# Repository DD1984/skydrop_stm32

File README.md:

this is port of SkyDrop vario to stm32vldiscovery board

origin code:
https://github.com/fhorinek/SkyDrop
website:
http://skybean.eu

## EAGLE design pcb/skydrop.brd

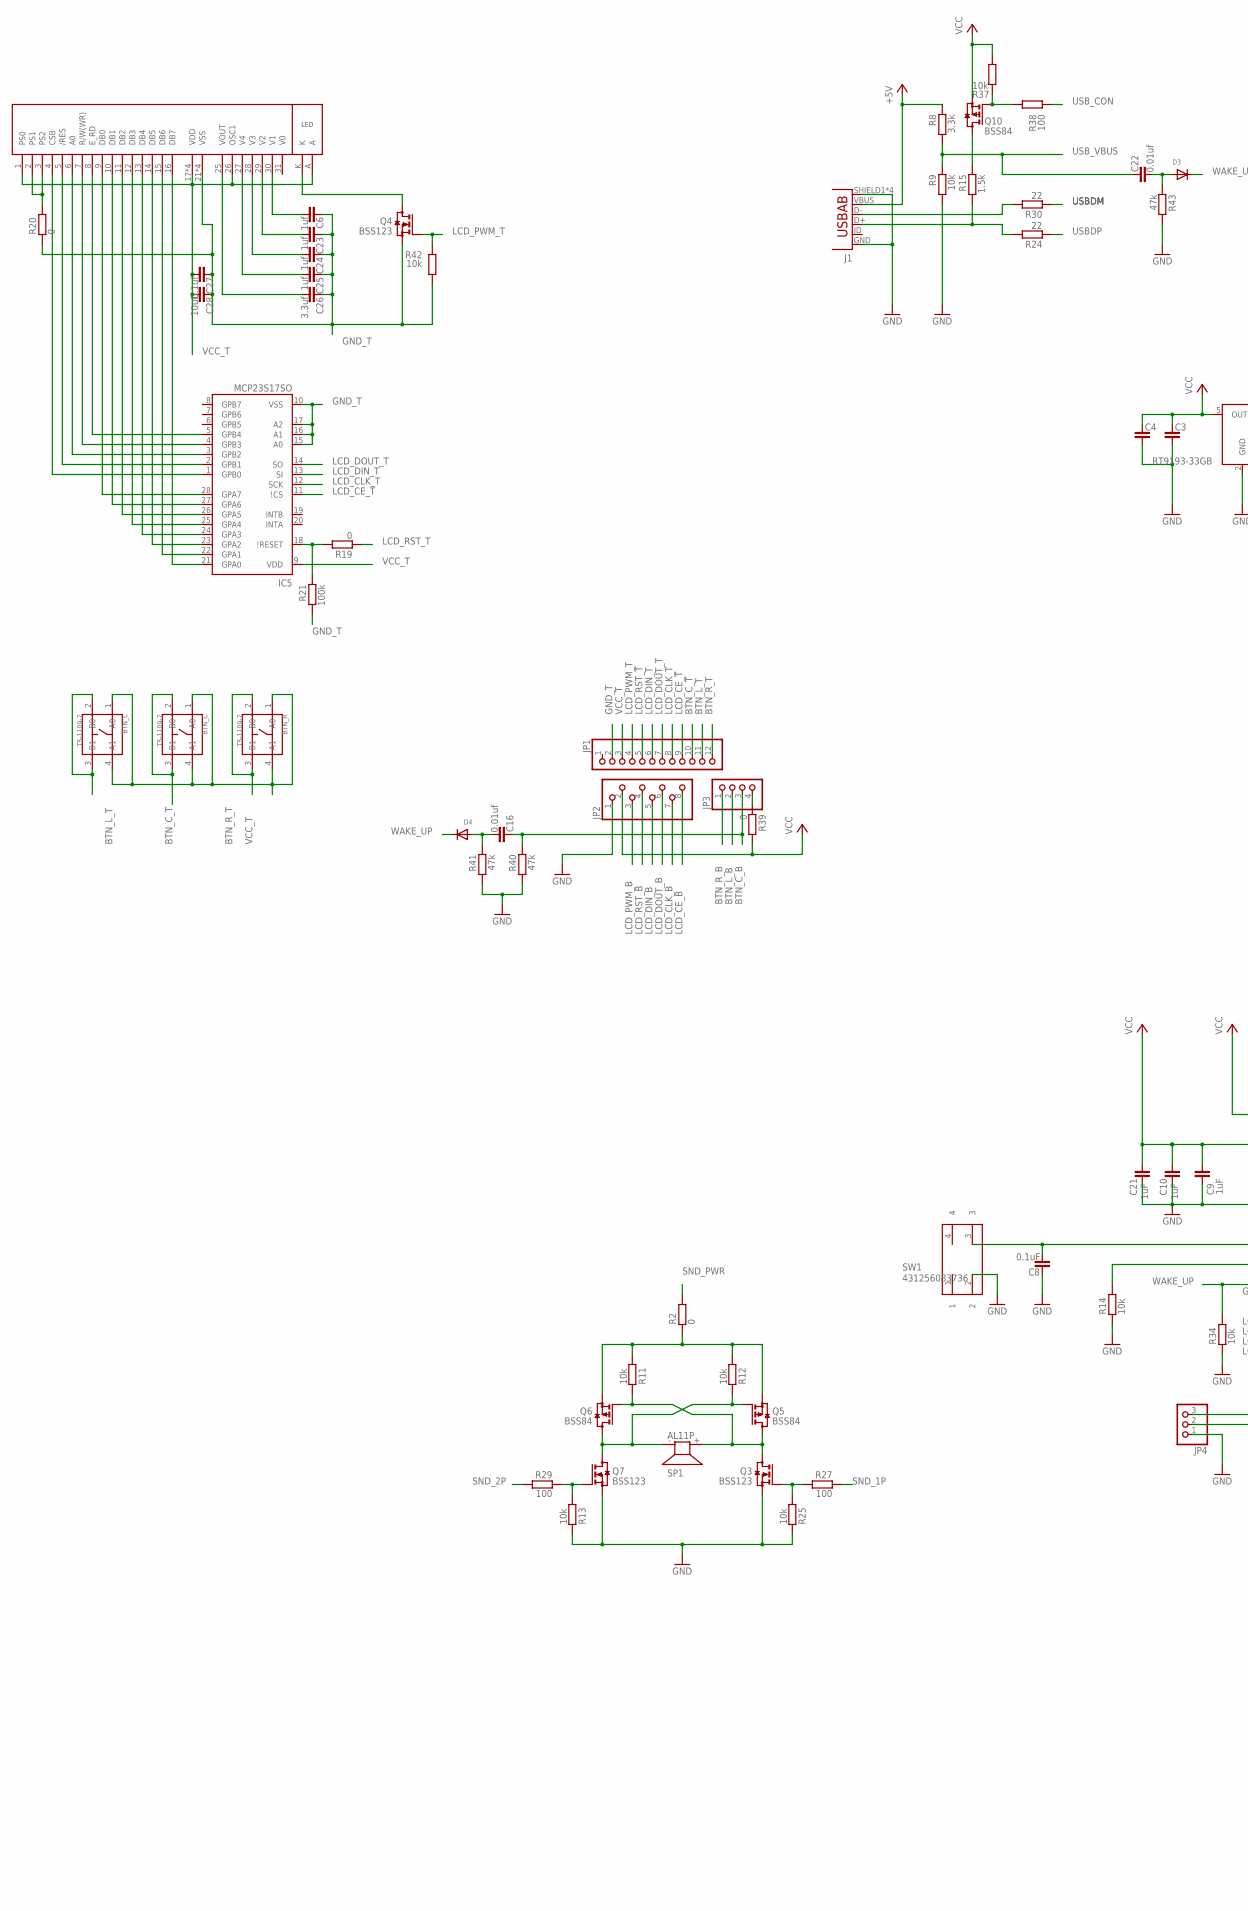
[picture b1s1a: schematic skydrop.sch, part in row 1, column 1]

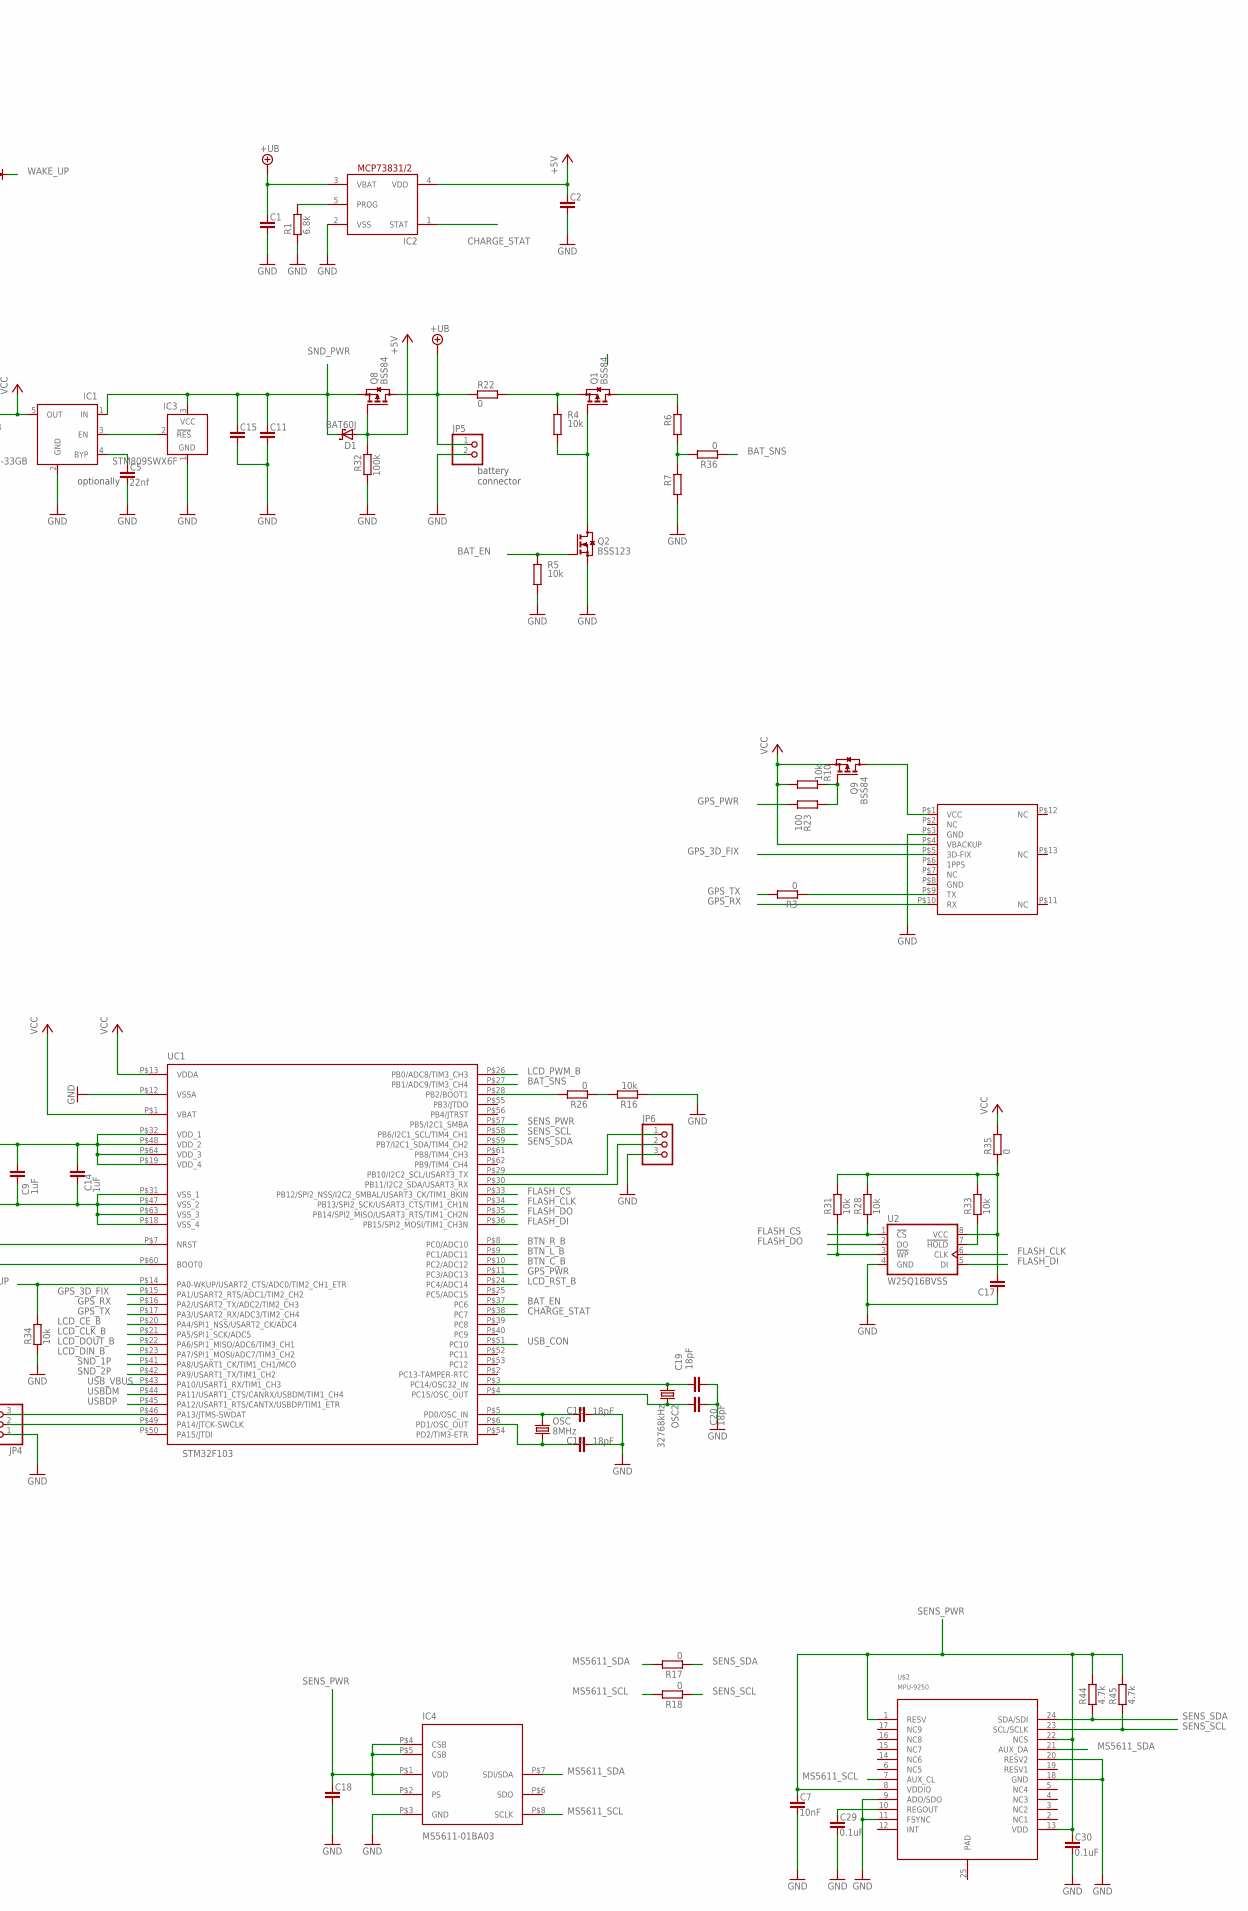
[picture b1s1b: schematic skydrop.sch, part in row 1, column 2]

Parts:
BTN_C: TS-1109-7; SW4-6.2X6.2X5.0MM
BTN_L: TS-1109-7; SW4-6.2X6.2X5.0MM
BTN_R: TS-1109-7; SW4-6.2X6.2X5.0MM
C1, C2, C3, C4, C11, C15, C17, C18: C_0805; C0805
C5: 22nf; C0805
C6, C23, C24, C25: 1uf; C0805
C7: 10nF; C0805
C8, C29, C30: 0.1uF; C0805
C9, C10, C14, C21: 1uF; C0805
C12, C13, C19, C20: 18pF; C0805
C16, C22: 0.01uf; C0805
C26: 3.3uf; C0805
C27: 0.1uf; C0805
C28: 10uf; C0805
D1: BAT60J; SOD323_ST
D3, D4: DIODE_SOD-123FL; SOD-123FL
IC1: RT9193-33GB; SOT23-5
IC2: MCP73831/OT; SOT23-5L
IC3: STM809SWX6F; SOT23B-3
IC4: MS5611-01BA03
IC5: MCP23S17SO; SO28W
J1: USB-AB; USB-AB-MICRO-SMD
JP1: PINHD-1X12; 1X12
JP2: PINHD-1X8; 1X08
JP3: PINHD-1X4; 1X04
JP4, JP6: PINHD-1X3; 1X03
JP5: PINHD-1X2; 1X02
OSC: 8MHz; HC49/S
OSC2: 32768kHz; MM20SS
Q1, Q5, Q6, Q8, Q9, Q10: BSS84; SOT23
Q2, Q3, Q4, Q7: BSS123; SOT23
R1: 6.8k; R0805
R2, R3, R17, R18, R19, R20, R22, R26, R35, R36, R39: 0; R1206
R4, R5, R9, R10, R11, R12, R13, R14, R16, R25, R28, R31, R33, R34, R37, R42: 10k; R0805
R6, R7: R_0805; R0805
R8: 3.3k; R0805
R15: 1.5k; R0805
R21, R32: 100k; R0805
R23, R27, R29, R38: 100; R0805
R24, R30: 22; R0805
R40, R41, R43: 47k; R0805
R44, R45: 4.7k; R0805
SP1: AL11P
SW1: 431256083736
U1: GPS_FGPMMOPA6C; FGPMMOPA6C
U2: W25Q16BVSS; SO08-SS
U$1: NOKIA5110
U$2: MPU-9250; LEAD-QFN24
UC1: STM32F103; TQFP-10X10-64

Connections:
+5V: C2.1, D1.A, IC2.4 (VDD), J1.VBUS, Q8.1 (G), R8.1, R32.1
+UB: C1.1, IC2.3 (VBAT), JP5.1, Q8.3 (D), R22.1
BAT_EN: Q2.1 (G), R5.1, UC1.P$37 (PC6)
BAT_SNS: R36.1, UC1.P$27 (PB1/ADC9/TIM3_CH4)
BTN_C_B: C16.1, JP3.3, R40.1, UC1.P$10 (PC2/ADC12)
BTN_C_T: BTN_C.2 (B0), BTN_C.3 (B1), JP1.10
BTN_L_B: JP3.2, UC1.P$9 (PC1/ADC11)
BTN_L_T: BTN_L.2 (B0), BTN_L.3 (B1), JP1.11
BTN_R_B: JP3.1, UC1.P$8 (PC0/ADC10)
BTN_R_T: BTN_R.2 (B0), BTN_R.3 (B1), JP1.12
CHARGE_STAT: IC2.1 (STAT), UC1.P$38 (PC7)
FLASH_CLK: U2.6 (CLK), UC1.P$34 (PB13/SPI2_SCK/USART3_CTS/TIM1_CH1N)
FLASH_CS: R28.1, U2.1 (!CS!), UC1.P$33 (PB12/SPI2_NSS/I2C2_SMBAL/USART3_CK/TIM1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)
FLASH_DI: U2.5 (DI), UC1.P$36 (PB15/SPI2_MOSI/TIM1_CH3N)
FLASH_DO: U2.2 (DO), UC1.P$35 (PB14/SPI2_MISO/USART3_RTS/TIM1_CH2N)
GND: C1.2, C2.2, C3.2, C4.2, C5.2, C7.2, C8.1, C9.1, C10.1, C11.2, C12.1, C13.1, C14.1, C15.2, C17.1, C18.2, C19.1, C20.1, C21.1, C29.2, C30.2, IC1.2 (GND), IC2.2 (VSS), IC3.1 (GND), IC4.P$3 (GND), J1.GND, J1.SHIELD1 (SHIELD), J1.SHIELD2 (SHIELD), J1.SHIELD3 (SHIELD), J1.SHIELD4 (SHIELD), JP2.1, JP4.1, JP5.2, JP6.3, Q2.2 (S), Q3.2 (S), Q7.2 (S), R1.1, R5.2, R7.2, R9.2, R13.1, R14.1, R16.1, R25.1, R32.2, R34.1, R40.2, R41.2, R43.2, SW1.2, U1.P$3 (GND), U2.4 (GND), U$2.9 (ADO/SDO), U$2.11 (FSYNC), U$2.18 (GND), U$2.20 (RESV2), UC1.P$12 (VSSA), UC1.P$18 (VSS_4), UC1.P$31 (VSS_1), UC1.P$47 (VSS_2), UC1.P$63 (VSS_3)
GND_T: C6.1, C23.1, C24.1, C25.1, C26.1, C27.1, C28.1, IC5.10 (VSS), IC5.15 (A0), IC5.16 (A1), IC5.17 (A2), JP1.2, Q4.2 (S), R20.1, R21.2, R42.2, U$1.21 (VSS), U$1.22 (VSS), U$1.23 (VSS), U$1.24 (VSS)
GPS_3D_FIX: U1.P$5 (3D-FIX), UC1.P$15 (PA1/USART2_RTS/ADC1/TIM2_CH2)
GPS_PWR: R23.2, UC1.P$11 (PC3/ADC13)
GPS_RX: U1.P$10 (RX), UC1.P$16 (PA2/USART2_TX/ADC2/TIM2_CH3)
GPS_TX: R3.2, UC1.P$17 (PA3/USART2_RX/ADC3/TIM2_CH4)
LCD_CE_B: JP2.8, UC1.P$20 (PA4/SPI1_NSS/USART2_CK/ADC4)
LCD_CE_T: IC5.11 (\!CS), JP1.9
LCD_CLK_B: JP2.7, UC1.P$21 (PA5/SPI1_SCK/ADC5)
LCD_CLK_T: IC5.12 (SCK), JP1.8
LCD_DIN_B: JP2.5, UC1.P$23 (PA7/SPI1_MOSI/ADC7/TIM3_CH2)
LCD_DIN_T: IC5.13 (SI), JP1.6
LCD_DOUT_B: JP2.6, UC1.P$22 (PA6/SPI1_MISO/ADC6/TIM3_CH1)
LCD_DOUT_T: IC5.14 (SO), JP1.7
LCD_PWM_B: JP2.3, UC1.P$26 (PB0/ADC8/TIM3_CH3)
LCD_PWM_T: JP1.4, Q4.1 (G), R42.1
LCD_RST_B: JP2.4, UC1.P$24 (PC4/ADC14)
LCD_RST_T: JP1.5, R19.1
MS5611_SCL: IC4.P$8 (SCLK), R18.2, U$2.7 (AUX_CL)
MS5611_SDA: IC4.P$7 (SDI/SDA), R17.2, U$2.21 (AUX_DA)
unnamed: Q5.2 (S), Q6.2 (S), R2.1, R11.2, R12.2
unnamed: IC2.5 (PROG), R1.2
unnamed: IC1.3 (EN), IC3.2 (!RES)
unnamed: Q7.1 (G), R13.2, R29.1
unnamed: C5.1, IC1.4 (BYP)
unnamed: C8.2, SW1.3, UC1.P$7 (NRST)
unnamed: Q1.1 (G), Q2.3 (D), R4.2
unnamed: Q1.2 (S), R4.1, R22.2
unnamed: IC5.18 (\!RESET), R19.2, R21.1
unnamed: R3.1, U1.P$9 (TX)
unnamed: Q9.1 (G), R10.1, R23.1
unnamed: Q3.1 (G), R25.2, R27.2
unnamed: R14.2, UC1.P$60 (BOOT0)
unnamed: JP4.3, UC1.P$46 (PA13/JTMS-SWDAT)
unnamed: JP4.2, UC1.P$49 (PA14/JTCK-SWCLK)
unnamed: R33.1, U2.7 (!HOLD!)
unnamed: C19.2, OSC2.1, UC1.P$3 (PC14/OSC32_IN)
unnamed: Q4.3 (D), U$1.K
unnamed: J1.D-, R30.2
unnamed: R31.1, U2.3 (!WP!)
unnamed: J1.D+, R15.2, R24.2
unnamed: Q9.3 (D), U1.P$1 (VCC)
unnamed: R26.2, UC1.P$28 (PB2/BOOT1)
unnamed: R16.2, R26.1
unnamed: JP6.1, UC1.P$29 (PB10/I2C2_SCL/USART3_TX)
unnamed: JP6.2, UC1.P$30 (PB11/I2C2_SDA/USART3_RX)
unnamed: Q1.3 (D), R6.1
unnamed: C20.2, OSC2.4 (2), UC1.P$4 (PC15/OSC_OUT)
unnamed: C17.2, R28.2, R31.2, R33.2, R35.1, U2.8 (VCC)
unnamed: R6.2, R7.1, R36.2
unnamed: Q10.1 (G), R37.1, R38.1
unnamed: C6.2, U$1.30 (V1)
unnamed: Q3.3 (D), Q5.3 (D), Q6.1 (G), R11.1, SP1.+ (2)
unnamed: Q5.1 (G), Q6.3 (D), Q7.3 (D), R12.1, SP1.- (1)
unnamed: Q10.3 (D), R15.1
unnamed: JP3.4, R39.1
unnamed: C16.2, D4.A, R41.1
unnamed: C22.2, D3.A, R43.1
unnamed: C23.2, U$1.29 (V2)
unnamed: C24.2, U$1.28 (V3)
unnamed: C25.2, U$1.27 (V4)
unnamed: C26.2, U$1.25 (VOUT)
unnamed: IC5.28 (GPA7), U$1.9 (DB0)
unnamed: IC5.27 (GPA6), U$1.10 (DB1)
unnamed: IC5.26 (GPA5), U$1.11 (DB2)
unnamed: IC5.25 (GPA4), U$1.12 (DB3)
unnamed: IC5.24 (GPA3), U$1.13 (DB4)
unnamed: IC5.23 (GPA2), U$1.14 (DB5)
unnamed: IC5.22 (GPA1), U$1.15 (DB6)
unnamed: IC5.21 (GPA0), U$1.16 (DB7)
unnamed: IC5.1 (GPB0), U$1.4 (CSB)
unnamed: IC5.2 (GPB1), U$1.5 (/RES)
unnamed: IC5.3 (GPB2), U$1.6 (A0)
unnamed: IC5.4 (GPB3), U$1.7 (R/W(WR))
unnamed: IC5.5 (GPB4), U$1.8 (E_RD)
unnamed: R20.2, U$1.2 (PS1), U$1.3 (PS2)
unnamed: C29.1, U$2.10 (REGOUT)
OSC_IN_5: C12.2, OSC.2, UC1.P$5 (PD0/OSC_IN)
OSC_OUT_6: C13.2, OSC.1, UC1.P$6 (PD1/OSC_OUT)
SENS_PWR: C7.1, C18.1, C30.1, IC4.P$1 (VDD), IC4.P$2 (PS), IC4.P$4 (CSB), IC4.P$5 (CSB), R44.2, R45.2, U$2.1 (RESV), U$2.8 (VDDIO), U$2.13 (VDD), U$2.22 (NCS), UC1.P$57 (PB5/I2C1_SMBA)
SENS_SCL: R18.1, R45.1, U$2.23 (SCL/SCLK), UC1.P$58 (PB6/I2C1_SCL/TIM4_CH1)
SENS_SDA: R17.1, R44.1, U$2.24 (SDA/SDI), UC1.P$59 (PB7/I2C1_SDA/TIM4_CH2)
SND_1P: R27.1, UC1.P$41 (PA8/USART1_CK/TIM1_CH1/MCO)
SND_2P: R29.2, UC1.P$42 (PA9/USART1_TX/TIM1_CH2)
SND_PWR: C11.1, C15.1, D1.C, IC1.1 (IN), IC3.3 (VCC), Q8.2 (S), R2.2
USBDM: R30.1, UC1.P$44 (PA11/USART1_CTS/CANRX/USBDM/TIM1_CH4)
USBDP: R24.1, UC1.P$45 (PA12/USART1_RTS/CANTX/USBDP/TIM1_ETR)
USB_CON: R38.2, UC1.P$51 (PC10)
USB_VBUS: C22.1, R8.2, R9.1, UC1.P$43 (PA10/USART1_RX/TIM1_CH3)
VCC: C3.1, C4.1, C9.2, C10.2, C14.2, C21.2, IC1.5 (OUT), JP2.2, Q9.2 (S), Q10.2 (S), R10.2, R35.2, R37.2, R39.2, U1.P$4 (VBACKUP), UC1.P$1 (VBAT), UC1.P$13 (VDDA), UC1.P$19 (VDD_4), UC1.P$32 (VDD_1), UC1.P$48 (VDD_2), UC1.P$64 (VDD_3)
VCC_T: BTN_C.1 (A0), BTN_C.4 (A1), BTN_L.1 (A0), BTN_L.4 (A1), BTN_R.1 (A0), BTN_R.4 (A1), C27.2, C28.2, IC5.9 (VDD), JP1.3, U$1.1 (PS0), U$1.17 (VDD), U$1.18 (VDD), U$1.19 (VDD), U$1.20 (VDD), U$1.26 (OSC1), U$1.A
WAKE_UP: D3.C, D4.C, R34.2, UC1.P$14 (PA0-WKUP/USART2_CTS/ADC0/TIM2_CH1_ETR)

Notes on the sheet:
battery connector
optionally

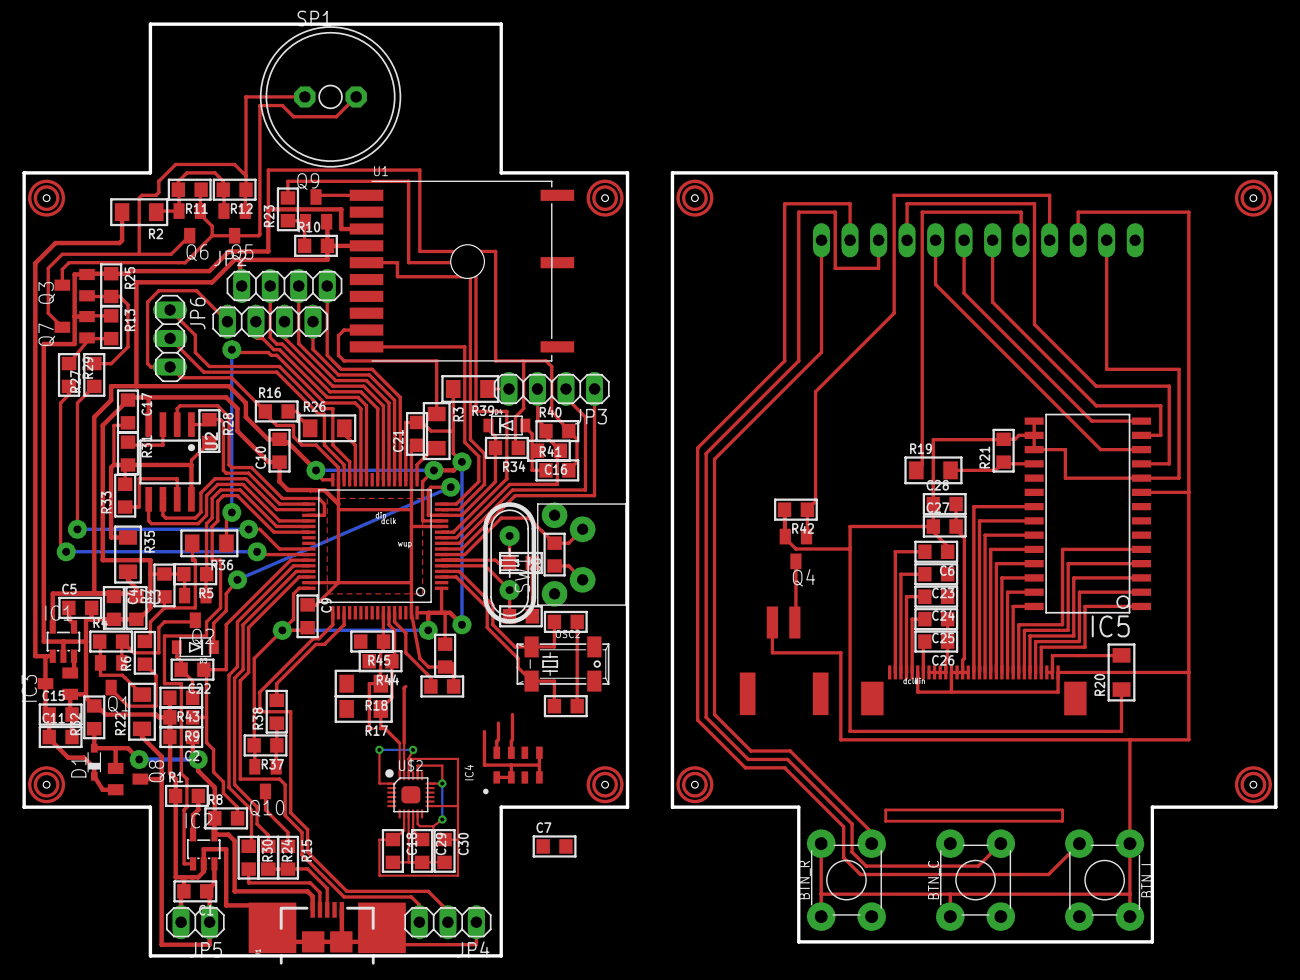
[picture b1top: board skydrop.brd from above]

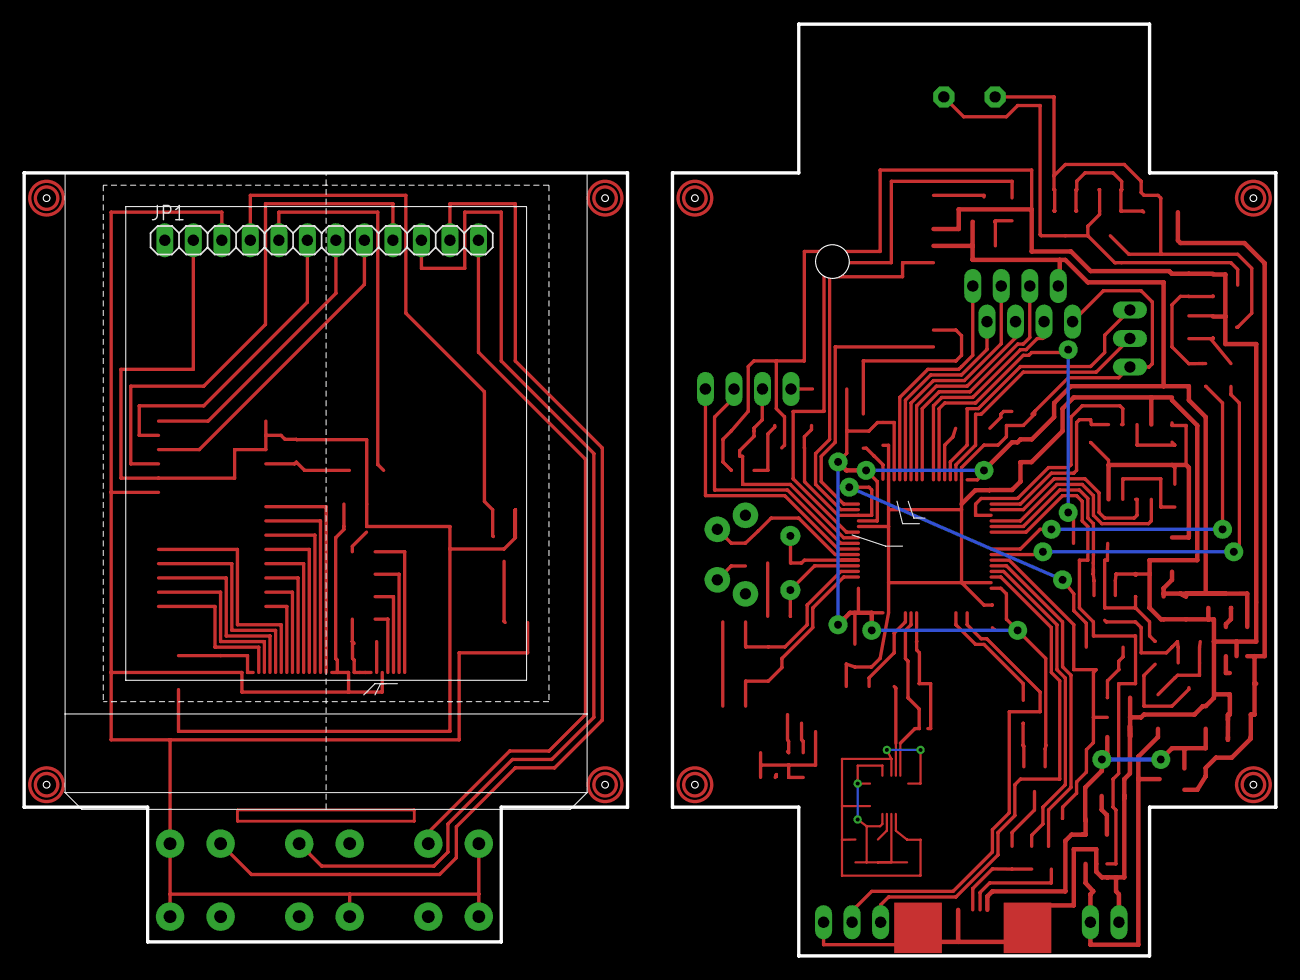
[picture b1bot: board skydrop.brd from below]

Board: 2 copper layers, 53.8 x 83.0 mm, 112 parts (2 on the bottom side), 107 nets.

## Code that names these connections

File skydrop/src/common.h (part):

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#define SWITCH1					porta3
#define GPS_TIMER				porta4
#define GPS_RESET				porta5
#define BAT_EN					porta6
#define BAT_SNS					porta7

#define SWITCH_INT				porta_interrupt0
#define GPS_TIMER_INT			porta_interrupt1
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//---------------- PORTE ---------------------
//SDA							porte0
//SCL							porte1
#define GPS_RX					porte2
#define GPS_TX					porte3
#define LEDB					porte4
#define BCKL					porte5
//X2 RTC TOSC2					porte6
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
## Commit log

2015-10-07 first stm32 build
2015-10-08 add hal files
2015-10-08 simple changes
2015-10-12 Makefile
2015-10-12 add other hal files
2015-10-12 first build with gui
2015-10-16 hal reorganosation
2015-10-16 GUI tasks form define to enum
2015-10-16 syscall for write to lcd
2015-10-16 init FILE *lcd_out
2015-10-16 some defines changes
2015-10-16 add display support for stm32 and add support TFT_ILI9163C - all veru ugly
2015-10-16 set_system: some code under define
2015-10-16 settings: some code under define
2015-10-16 add button support for stm32
2015-10-16 linkage lcd output function for C and C++
2015-10-16 change Makefile, remember -O1 instead -Os
2015-10-16 error in type cast in font in lcd:write
2015-10-16 button rebind adn fix uart output
2015-10-19 add hal files for timers
2015-10-19 remove STM32 define from fonts - restore PROGMEM
2015-10-19 ls scripts - temporarily set ram end to 0x20001FF8 - needed for stack aligment(8) - for printf_float work
2015-10-19 redefine button, because pin pa1 are used for sound pwm
2015-10-19 remove STM32 define
2015-10-19 add battery stub, remove define BATTERY_SUPPORT, change define BUZZER_SUPPORT to AUDIO_SUPPORT
2015-10-19 add timers init hal functions
2015-10-19 remove widget constant numbers and change it to enum
2015-10-19 audio driver for stm32
2015-10-19 change BUZZER_SUPPORT define to AUDIO_SUPPORT
2015-10-19 remove STM32 define for PROGMEM
2015-10-19 add some code under RTC_SUPPORT
2015-10-19 default config support
2015-10-19 PROGMEM, pgm_read_* realisation for stm32
2015-10-21 fully worked audio driver
2015-10-29 remove audio_step call from tick intrrupt
2015-10-29 hal i2c support and dedicated file for timer interrupt handlers
2015-10-29 add bmp180 support
2015-10-29 rename audio timer handler
2015-10-29 remove second i2c init functions
2015-10-29 bmp180 support fc_meas_timer handler kalman filter with variable parameter for debug use
2015-11-04 hal reorganization
2015-11-04 simple eeprom realisation, w/o power loss protection
2015-11-05 - add hal file for power control and rtc - add rtc support with hal modification (not good, but simple) - system reset realisation
2015-11-05 add StandBY mode
2015-11-06 add menu items GPS under define
2015-11-09 move ILI9163C support to separate files
2015-11-09 remove define DISPLAY_SUPPORT
2015-11-09 change #ifdef FC_TIMER to #ifndef STM32
2015-11-09 remove define RTC_SUPPORT
2015-11-09 remove define AUDIO_SUPPORT
2015-11-09 remove define UART_SUPPORT
2015-11-10 remove define WDT_SUPPORT, but wdt not implemented
2015-11-14 change timers MspInit function
2015-11-14 remove bmp180 support and add ms5611
2015-11-14 debug print - unbuffering output
2015-11-14 restore original kalman filter code, filter init w/o new
2015-11-14 makefile and debug message about heap and stack collision
2015-11-15 - temperature from ms5611 - data structures for acc and gyro and its widget under define
2015-11-15 additional for prevision commit
2015-11-15 add mass storage settings under define, and fix bug with widgets
2015-11-15 enable 5110 support
2015-11-15 poll buttons one time in mstick
2015-11-20 1. check PROM crc for ms5611 2. buzzer to tim1 for synphase signal to buzzer 3. lcd off in powerdown
2015-11-20 edit README.md1
2015-11-24 start pcb design
2015-12-30 bat adc
2016-01-02 bat support
2016-08-03 hal for stm32f103xe
2016-08-03 stm32f103 i2c work with hack
2016-08-03 [103] ld scripts - temporarily set ram end to 0x20001FF8 - needed for stack aligment(8) - for printf_float work
2016-08-03 ld script 103 - add eeprom section
2016-08-04 rotate display
2016-11-15 - change uart1->uart3 - change display and keys mapping - add H-bridge support
2016-11-17 battery remap, check usb power and charge status
2016-11-17 power_down - default task
2016-11-24 pcb in eagle
2016-12-04 change buttons, bat_en mapping, remove N pwm func
2016-12-04 pcb improovment, gitignore change
2016-12-07 start spi flash support
2016-12-08 add files to gitignore
2016-12-08 add eagle lck file to gitignore
2016-12-08 start usb support
2016-12-08 restore pcb
2016-12-08 change usb disconnect pin
2016-12-08 usb clock
2016-12-08 gitignore
2016-12-09 spi flash driver improovment
2016-12-09 usb flash support, note: only 512b from 4kb sector support
2016-12-10 add 4kb flash sector support
2016-12-11 add exFat support
2016-12-12 first build with logger support
2016-12-12 first build with gps support
2016-12-14 fix after merge
2016-12-14 fix after merge #2
2016-12-14 fix after merge #3
2016-12-14 first successeful build after merge
2016-12-14 half fix: time, debug, task_timer
2016-12-17 - fix reset status - temporary comment gps uart function - add button port cloock enable
2016-12-17 fix battery indicator
2016-12-17 usb MS fix
2016-12-17 - stop fc_meas_timer before ms5611 poweroff - decrease clock 72MHZ -> 48mHZ for smt32 internal flash write work - may be need to use FLASH_SR_EOP instead FLASH_SR_BSY - unmount fs
2016-12-18 eeprom impovement
2016-12-18 - place config_ro from .cfg_ro to eeprom section - reset flash configuration after stlink programming - for eeprom work after programming
2016-12-19 add stop fc_meas_timer before start, add start ms5611 measurement
2016-12-19 set baro valid timer to old 12s value - temporary
2016-12-21 fix: battry charge status
2016-12-21 audio: delete unused code
2017-01-05 - change buttons poll freq - first power on always in active task
2017-01-05 deep power mode for spi flash
2017-01-06 - SysTick priority more then usb irq priority - for delay work in usb irq - deinit usb
2017-01-06 fix debug log
2017-01-11 start gps uart support
2017-01-11 fix gps uart deinit
2017-01-11 fix battery callibration
2017-01-12 change %S->%s
2017-01-12 remove LOGGER_SUPPORT define from logger.cpp
2017-01-13 comment f_sync in logger - this is very slowly on spi flash and not needed at all with battry power
2017-01-18 fix vario & demo vario
2017-01-19 fix time setup on first power on
2017-01-20 reading from gps uart only if it initialized
2017-01-22 add DEBUG macro for C source
2017-01-22 fix two crashes in usb without host (only charger)
2017-01-23 improve pcb
2017-01-30 [pcb] new display
2017-03-10 improve pcb for new display
2017-03-10 display docs
2017-03-10 wdg support
2017-05-25 add spi extender
2017-05-25 improove spi extender
2017-05-29 [pcb] improove
2017-05-30 [pcb] improve
